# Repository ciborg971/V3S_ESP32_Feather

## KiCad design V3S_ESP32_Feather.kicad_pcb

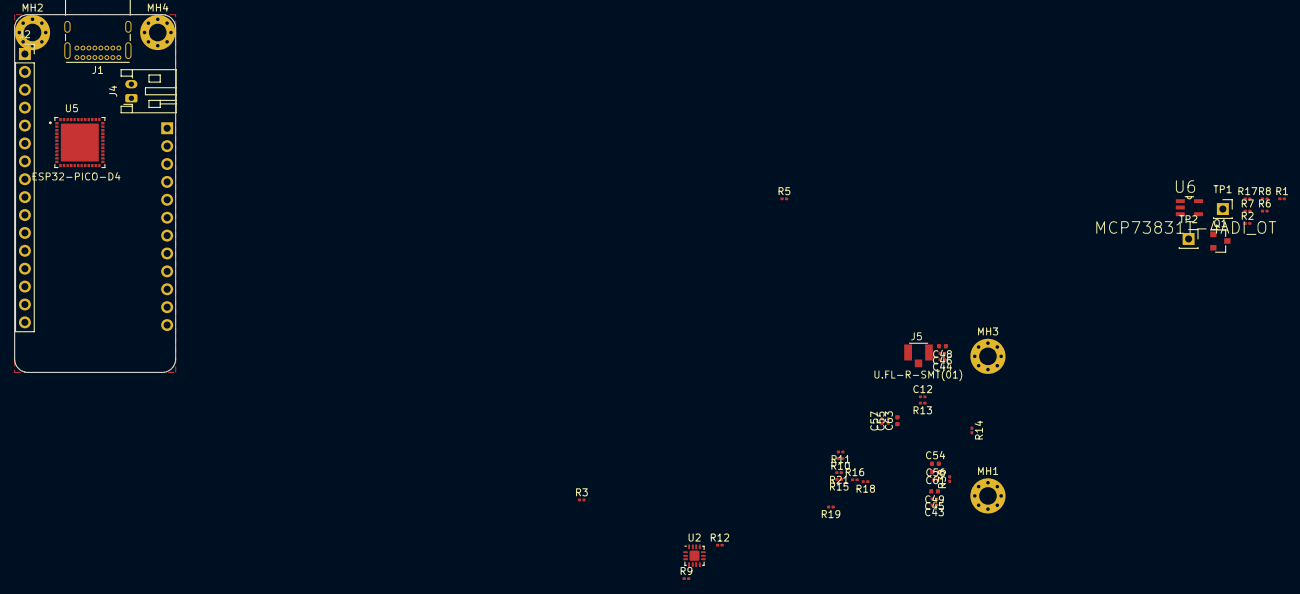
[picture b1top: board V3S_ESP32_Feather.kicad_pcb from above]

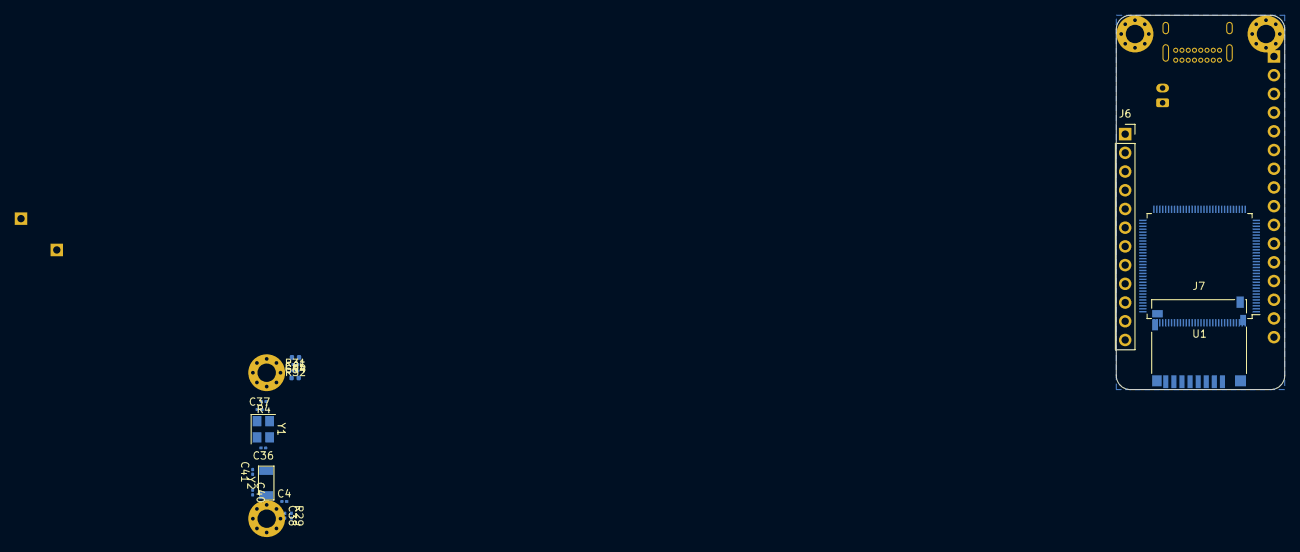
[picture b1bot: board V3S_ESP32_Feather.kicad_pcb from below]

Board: 4 copper layers, 22.9 x 50.8 mm, 64 parts (17 on the bottom side), 73 nets, no tracks yet.

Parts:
C4: 4.7uF; C_0201_0603Metric
C12: 0.1uF; C_0201_0603Metric
C36, C37: 18pF; C_0201_0603Metric
C38, C45, C46, C57: 1uF; C_0201_0603Metric
C40, C41: 20pF; C_0201_0603Metric
C43, C44, C55, C56: 10uF; C_0201_0603Metric
C48, C49, C54, C61, C63, C64, C65: 100nF; C_0402_1005Metric
J1: USB_C_Receptacle_USB2.0; USB_C_Receptacle_GCT_USB4085
J2: Header16; PinSocket_1x16_P2.54mm_Vertical
J4: BAT; JST_PH_S2B-PH-K_1x02_P2.00mm_Horizontal
J5: U.FL-R-SMT(01); HRS_U.FL-R-SMT(01)
J6: Header12; PinSocket_1x12_P2.54mm_Vertical
J7: Micro_SD_Card_Det; microSD_HC_Hirose_DM3D-SF
MH1, MH2, MH3, MH4: MountingHole_Pad; MountingHole_2.5mm_Pad_Via
Q1: S8050(SOT-23); SOT-23
R1, R7: 0; R_0201_0603Metric
R2, R6: 100K; R_0201_0603Metric
R3, R5, R12: 10K; R_0201_0603Metric
R4: 240R 1%; R_0201_0603Metric
R8, R10, R11, R29: 2K; R_0201_0603Metric
R9: 47K; R_0201_0603Metric
R13, R14, R15, R16, R18, R19, R21: 50K; R_0201_0603Metric
R17: 470R; R_0201_0603Metric
R30: 6K 1%; R_0201_0603Metric
R31, R32: 2K 1%; R_0201_0603Metric
TP1: PWR_SRC; PinSocket_1x01_P2.54mm_Vertical
TP2: CHRG_IN; PinSocket_1x01_P2.54mm_Vertical
U1: V3S; LQFP-128_14x14mm_P0.4mm
U2: FUSB302B01MPX; WQFN-14-1EP_2.5x2.5mm_P0.5mm_EP1.45x1.45mm
U5: ESP32-PICO-D4; PQFN50P700X700X104-49N
U6: MCP73831T-4ADI_OT; SOT95P280X145-5N
Y1: X1E0000210832; Crystal_SMD_3225-4Pin_3.2x2.5mm
Y2: CC5V-T1A 32.768KHZ +-20PPM 12.5PF; SOIC-2

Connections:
+1V2: C55.1, C57.1, C63.1, U1.19, U1.20, U1.21, U1.25, U1.26, U1.38, U1.47, U1.51, U1.56, U1.58, U1.64, U1.80, U1.88, U1.108, U1.126
+1V8: C43.1, C45.1, C49.1, C64.2, R10.1, R11.1, R31.2, U1.59, U1.60, U1.61, U1.62, U1.65, U1.66, U1.67, U1.68, U1.69, U1.70, U1.72, U1.79, U1.85
+3.3VA: C44.1, C46.1, C48.1, C54.1, C56.1, C61.2, U1.50, U1.57, U1.76, U1.93, U1.104, U1.109, U1.115, U1.127
+3V3: J2.2, J7.4, R3.1, R5.1, R9.1, R12.2, R16.2, R18.2, R19.2, R21.2, R29.1, U1.122, U2.3, U2.4, U5.1, U5.3, U5.4, U5.19, U5.37, U5.43, U5.46
+BATT: J4.2, J6.1, Q1.3, U6.3
/AIN0: J2.5, U5.15
/AIN1: J2.6, U5.14
/AIN2: J2.7, U5.8
/AIN3: J2.8, U5.5
/AIN4: J2.9, U5.6
/AIN5: J2.10, U5.7
/All V3s input output/CSI_I2C_SCL: R11.2, U1.9
/All V3s input output/CSI_I2C_SDA: R10.2, U1.8
/All V3s input output/I2C0_CLK: U1.45, U2.6
/All V3s input output/I2C0_SDA: U1.46, U2.7
/All V3s input output/PF0: J7.8, U1.107
/All V3s input output/PF1: J7.7, U1.106
/All V3s input output/PF2: J7.5, U1.105
/All V3s input output/PF3: J7.3, U1.103
/All V3s input output/PF4: J7.2, U1.102
/All V3s input output/PF5: J7.1, R9.2, U1.101
/All V3s input output/RST: C38.2, R29.2, U1.99
/All V3s input output/SDIO1_CLK: U1.5, U5.17
/All V3s input output/SDIO1_CMD: R21.1, U1.4, U5.21
/All V3s input output/SDIO1_DAT0: R15.1, U1.3, U5.22
/All V3s input output/SDIO1_DAT1: R16.1, U1.2, U5.24
/All V3s input output/SDIO1_DAT2: R18.1, U1.1, U5.18
/All V3s input output/SDIO1_DAT3: R19.1, U1.128, U5.20
/All V3s input output/USB_INT: U1.100, U2.5
/CC1: J1.A5, U2.10, U2.11
/CC2: J1.B5, U2.1, U2.14
/FreePin: J2.16, U5.34
/GPIO0: J6.10, U5.16
/GPIO1: J6.9, U5.12
/GPIO2: J6.8, U5.13
/GPIO3: J6.7, U5.10
/GPIO4: J6.6, U5.11
/GPIO5: J6.5, U5.28
/GPIO6: J6.4, U5.29
/I2C_SCL: J6.11, R3.2, U5.39
/I2C_SDA: J6.12, R5.2, U5.42
/MISO: J2.13, U5.38
/MOSI: J2.12, U5.36
/PMIC Power Battery/SVREF: C64.1, C65.2, R31.1, R32.2, U1.63, U1.71
/PMIC Power Battery/VBUS: R1.1, R7.2
/PMIC Power Battery/VCC_PE: U1.12, U1.29
/SCK: J2.11, U5.35
/UART_RX_D0: J2.14, U1.48
/UART_TX_D0: J2.15, U1.49
/USB_D_N: J1.A7, J1.B7, U1.110
/USB_D_P: J1.A6, J1.B6, U1.111
/VBUS: J1.A4, J1.A9, J1.B4, J1.B9, J6.3, U2.2, U2.12, U2.13
/WIFI, BT, RT/EN: C12.1, R13.2, U1.42
/WIFI, BT, RT/IO0: R14.1, U5.23
/WIFI, BT, RT/IO0_PULL: R14.2, U1.41
/WIFI, BT, RT/IO2_PULL: R15.2, U1.15
/WIFI, BT, RT/UART0_RX: U1.39, U5.40
/WIFI, BT, RT/UART0_TX: U1.40, U5.41
GND: C4.1, C12.2, C36.2, C37.2, C38.1, C40.1, C41.1, C43.2, C44.2, C45.2, C46.2, C48.2, C49.2, C54.2, C55.2, C56.2, C57.2, C61.1, C63.2, C65.1, J1.A1, J1.A12, J1.B1, J1.B12, J1.S1, J2.4, J5.1, J5.2, J7.6, MH1.1, MH2.1, MH3.1, MH4.1, R2.2, R4.2, R8.2, R30.1, R32.1, U1.116, U1.117, U1.118, U1.123, U2.8, U2.9, U2.15, U5.49, U6.2, Y1.2, Y1.4
unnamed: Q1.2, R6.2
unnamed: C4.2, U1.97
unnamed: C36.1, U1.75, Y1.3
unnamed: C37.1, U1.74, Y1.1
unnamed: C40.2, U1.96, Y2.1
unnamed: C41.2, U1.95, Y2.2
unnamed: Q1.1, R1.2, R2.1, TP1.1
unnamed: J5.3, U5.2
unnamed: R4.1, U1.73
unnamed: R7.1, TP2.1, U6.4
unnamed: R8.1, U6.5
unnamed: R13.1, U5.9
unnamed: R17.2, U6.1
unnamed: R30.2, U1.94
